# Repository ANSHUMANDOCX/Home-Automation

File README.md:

# ESP32 Home automation
## Description 
- This is a ESP32 S3 Based Home Automation devices which has 6 Relay switches that can be controlled over the web 
- It also has a BME280 Sensor for monitoring temprature,humidity and pressure in the realtime and can be monitored using a mobile app or a Webpage.
- Also had a FTDI header for easy programming
- Along with web control there is provison to add any physical switches and the case has space to add touch switches too
## Parts Used
- ESP32 S3
- BME280 Sensor
- 6 relays
- Hi-Link 20w 5v AC-DC converter
## Usage 
it is very simple to use just need to plugin the FTDI programmer and Upload the code after adding your SSID nad password so that it will work and on you browser open 192.168.1.100 ive set this as the static IP for accessing the webpage running on the ESP

## PCB Schematic and CAD 

## BUILD 

demo link https://drive.google.com/file/d/14zfI7igBqzAfgmiqQ8RciHNbKA9al0T5/view?usp=sharing

## BOM 
| Name                     | Purpose                     | Quantity | Total Cost (USD) | Link                                                                 | Distributor |
|--------------------------|----------------------------|----------|------------------|----------------------------------------------------------------------|-------------|
| Passive Components       | Ressitor and ETC           | 1        | 3.00             |                                                                      | LCSC        |
| BWGMRJWX50-10WJ          | Antenna Stem               | 1        | 0.94             |                                                                      | LCSC        |
| BWIPX1-SMA-1.13L100      | Antenna                    | 1        | 0.94             |                                                                      | LCSC        |
| MIC5219-3.3YM5-TD        | 3.3v Regulator             | 1        | 1.23             | https://www.lcsc.com/product-detail/C42422052.html                  | LCSC        |
| SMBJ5.0A                 | TVS diode                  | 1        | 0.50             | https://www.lcsc.com/product-detail/C83333.html                     | LCSC        |
| DB128V-5.0-2P-BK-S       | Terminal Block 2P          | 1        | 0.80             | https://www.lcsc.com/product-detail/C424692.html                    | LCSC        |
| 1N4007 M7                | Diode                      | 1        | 0.64             | https://www.lcsc.com/product-detail/C20754788.html                  | LCSC        |
| TS665CJ                  | Switch                     | 1        | 0.83             | https://www.lcsc.com/product-detail/C393938.html                    | LCSC        |
| DB128V-5.08-3P-GN-S      | Terminal Block 3P          | 1        | 1.45             | https://www.lcsc.com/product-detail/C2915640.html                   | LCSC        |
| MOV14D471K206RV080       | its a MOV for protection   | 1        | 0.52             | https://www.lcsc.com/product-detail/C22390366.html                  | LCSC        |
| ESP32-S3-WROOM-1-N4      | the brains                 | 1        | 4.64             | https://www.lcsc.com/product-detail/C2913197.html                   | LCSC        |
| BME280                   | Sensor                     | 1        | 7.24             | https://www.lcsc.com/product-detail/C92489.html                     | LCSC        |
| Relay 5v                 | to switch                  | 6        | 2.88             | https://www.lcsc.com/product-detail/C35449.html                     | LCSC        |
| PC817C                   | optocoupler                | 1        | 0.55             | https://www.lcsc.com/product-detail/C20612594.html                  | LCSC        |
| HLK-20M05                | onboard 5v                 | 1        | 4.58             | https://www.lcsc.com/product-detail/C465406.html                    | LCSC        |

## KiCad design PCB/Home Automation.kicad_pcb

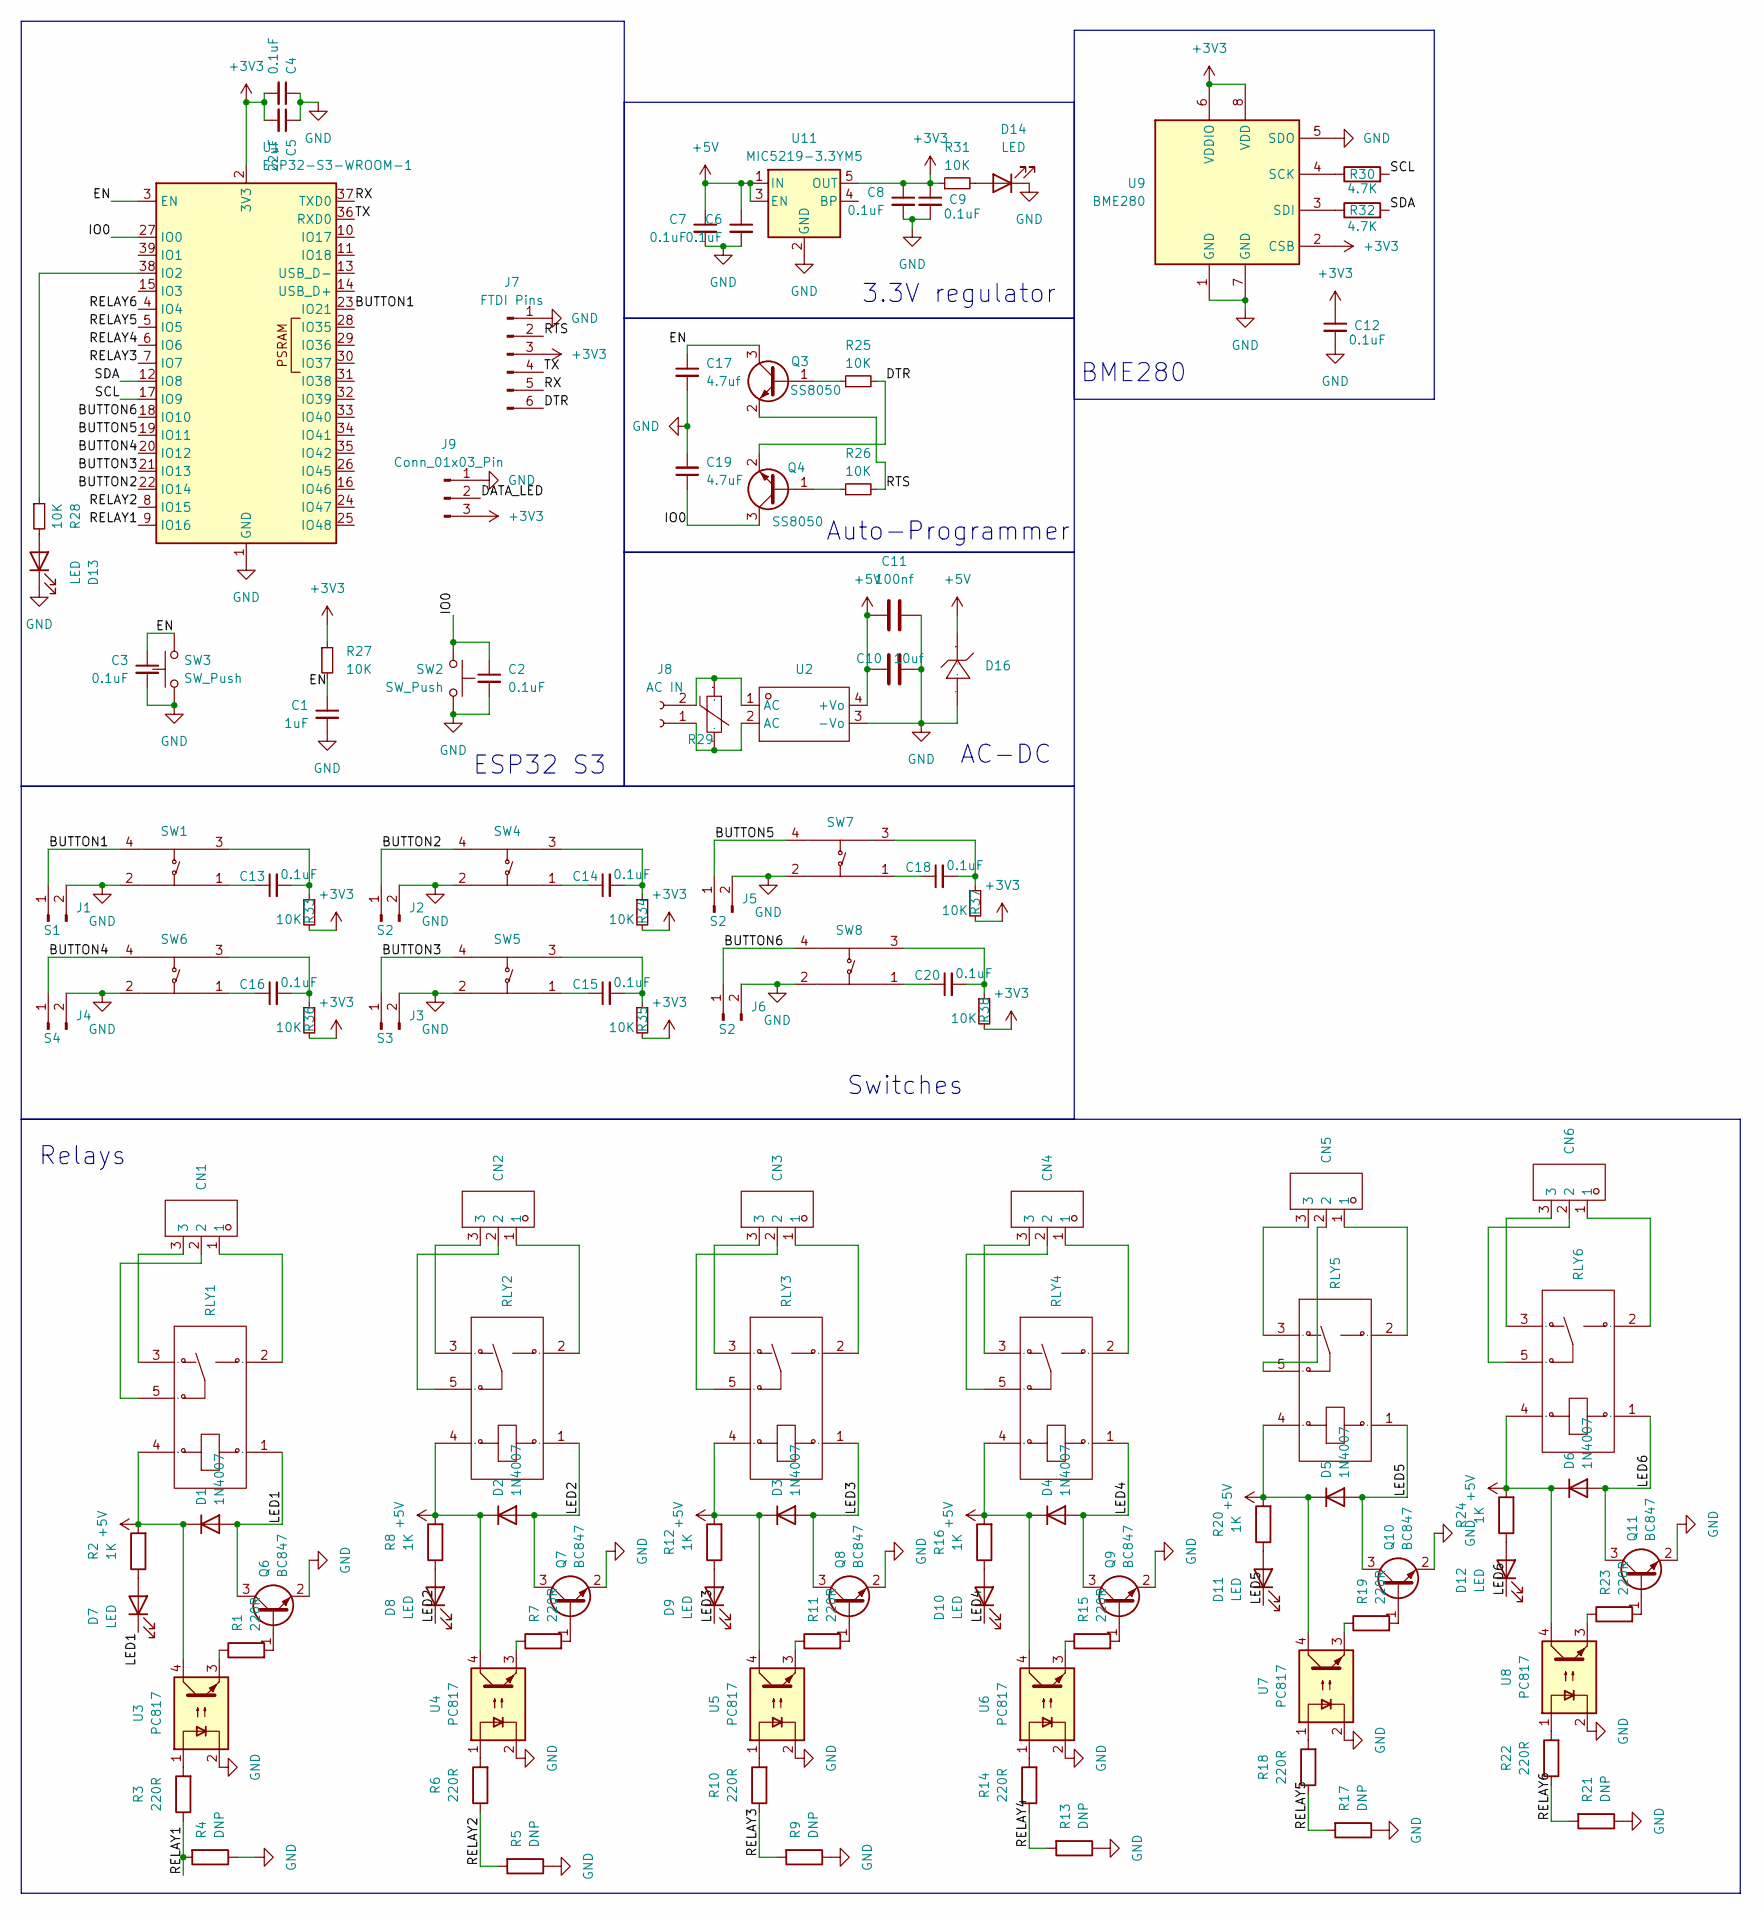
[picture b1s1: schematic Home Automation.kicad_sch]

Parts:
C1: 1uF; C_0603_1608Metric
C2, C3, C4, C6, C7, C8, C9, C12, C13, C14, C15, C16, C18, C20: 0.1uF; C_0603_1608Metric
C5: 22uF; C_0603_1608Metric
C10: 10uf; C_0603_1608Metric
C11: 100nf; C_0603_1608Metric
C17: 4.7uf; C_0603_1608Metric_Pad1.08x0.95mm_HandSolder
C19: 4.7uF; C_0603_1608Metric_Pad1.08x0.95mm_HandSolder
CN1, CN2, CN3, CN4, CN5, CN6: CONN-TH_3P-P5.08_DIBO_DB128V-5.08-3P-X; Manufacturer Part DB128V-5.08-3P-GN-S; LCSC Part Name 1x3P 5.08mm 直插 排数:1 每排P数:3
D1, D2, D3, D4, D5, D6: 1N4007; D_SMA
D7, D8, D9, D10, D11, D12, D14: LED; LED_0805_2012Metric
D13: LED; LED_0603_1608Metric_Pad1.05x0.95mm_HandSolder
D16: SMB_L4.6-W3.6-LS5.3-RD; Manufacturer Part SMBJ5.0A; LCSC Part Name SMBJ5.0A
J1: S1; PinHeader_1x02_P2.54mm_Vertical
J2, J5, J6: S2; PinHeader_1x02_P2.54mm_Vertical
J3: S3; PinHeader_1x02_P2.54mm_Vertical
J4: S4; PinHeader_1x02_P2.54mm_Vertical
J7: FTDI Pins; PinHeader_1x06_P2.54mm_Vertical
J8: AC IN; TerminalBlock_CUI_TB007-508-02_1x02_P5.08mm_Horizontal
J9: Conn_01x03_Pin; PinHeader_1x03_P2.54mm_Vertical
Q3, Q4: SS8050; SOT-23
Q6, Q7, Q8, Q9, Q10, Q11: BC847; SOT-23
R1, R3, R6, R7, R10, R11, R14, R15, R18, R19, R22, R23: 220R; R_0603_1608Metric
R2, R8, R12, R16, R20, R24: 1K; R_0603_1608Metric
R4, R5, R9, R13, R17, R21: DNP; R_0603_1608Metric
R25, R26: 10K; R_0603_1608Metric_Pad0.98x0.95mm_HandSolder
R27, R28, R31, R33, R34, R35, R36, R37, R38: 10K; R_0603_1608Metric
R29: 430pF@1kHz; RES-TH_L16.0-W5.2-P7.50-D0.8-S4.20; Manufacturer Part MOV14D471K206RV080; LCSC Part Name 14D471K
R30, R32: 4.7K; R_0603_1608Metric
RLY1, RLY2, RLY3, RLY4, RLY5, RLY6: RELAY-TH_SRD-XXVDC-XL-C; Manufacturer Part SRD-05VDC-SL-C; LCSC Part Name 蓝色 单组转换型继电器
SW1, SW4, SW5, SW6, SW7, SW8: SW-TH_4P-L6.0-W6.0-P4.50-LS6.5; Manufacturer Part TS665CJ; LCSC Part Name 6*6*5mm 直插 轻触开关
SW2, SW3: SW_Push; SW_Push_SPST_NO_Alps_SKRK
U1: ESP32-S3-WROOM-1
U2: PWRM-TH_HLK-20MXX; Manufacturer Part HLK-20M05; LCSC Part Name 20W超紧凑型电源模块系列
U3, U4, U5, U6, U7, U8: PC817; DIP-4_W7.62mm
U9: BME280; Bosch_LGA-8_2.5x2.5mm_P0.65mm_ClockwisePinNumbering
U11: MIC5219-3.3YM5; SOT-23-5

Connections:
+3V3: C4.2, C5.2, C8.1, C9.1, C12.1, J7.3, J9.3, R27.1, R31.1, R33.2, R34.2, R35.2, R36.2, R37.2, R38.2, U1.2 (3V3), U9.2 (CSB), U9.6 (VDDIO), U9.8 (VDD), U11.5 (OUT)
+5V: C6.1, C7.1, C10.1, C11.1, D1.1 (K), D2.1 (K), D3.1 (K), D4.1 (K), D5.1 (K), D6.1 (K), D16.1 (C), R2.2, R8.2, R12.2, R16.2, R20.2, R24.2, RLY1.4, RLY2.4, RLY3.4, RLY4.4, RLY5.4, RLY6.4, U2.4 (+Vo), U3.4, U4.4, U5.4, U6.4, U7.4, U8.4, U11.1 (IN), U11.3 (EN)
/BUTTON1: J1.1, SW1.4 (D), U1.23 (IO21)
/BUTTON2: J2.1, SW4.4 (D), U1.22 (IO14)
/BUTTON3: J3.1, SW5.4 (D), U1.21 (IO13)
/BUTTON4: J4.1, SW6.4 (D), U1.20 (IO12)
/BUTTON5: J5.1, SW7.4 (D), U1.19 (IO11)
/BUTTON6: J6.1, SW8.4 (D), U1.18 (IO10)
/DTR: J7.6, Q4.2 (E), R25.2
/EN: C1.1, C3.1, C17.1, Q3.3 (C), R27.2, SW3.2, U1.3 (EN)
/IO0: C2.1, C19.1, Q4.3 (C), SW2.2, U1.27 (IO0)
/LED1: D1.2 (A), D7.1 (K), Q6.3 (C), RLY1.1
/LED2: D2.2 (A), D8.1 (K), Q7.3 (C), RLY2.1
/LED3: D3.2 (A), D9.1 (K), Q8.3 (C), RLY3.1
/LED4: D4.2 (A), D10.1 (K), Q9.3 (C), RLY4.1
/LED5: D5.2 (A), D11.1 (K), Q10.3 (C), RLY5.1
/LED6: D6.2 (A), D12.1 (K), Q11.3 (C), RLY6.1
/RELAY1: R3.1, R4.2, U1.9 (IO16)
/RELAY2: R5.2, R6.1, U1.8 (IO15)
/RELAY3: R9.2, R10.1, U1.7 (IO7)
/RELAY4: R13.2, R14.1, U1.6 (IO6)
/RELAY5: R17.2, R18.1, U1.5 (IO5)
/RELAY6: R21.2, R22.1, U1.4 (IO4)
/RTS: J7.2, Q3.2 (E), R26.2
/RX: J7.5, U1.37 (TXD0)
/SCL: R30.2, U1.17 (IO9)
/SDA: R32.2, U1.12 (IO8)
/TX: J7.4, U1.36 (RXD0)
GND: C1.2, C2.2, C3.2, C4.1, C5.1, C6.2, C7.2, C8.2, C9.2, C10.2, C11.2, C12.2, C17.2, C19.2, D13.1 (K), D14.1 (K), D16.2 (A), J1.2, J2.2, J3.2, J4.2, J5.2, J6.2, J7.1, J9.1, Q6.2 (E), Q7.2 (E), Q8.2 (E), Q9.2 (E), Q10.2 (E), Q11.2 (E), R4.1, R5.1, R9.1, R13.1, R17.1, R21.1, SW1.2 (B), SW2.1, SW3.1, SW4.2 (B), SW5.2 (B), SW6.2 (B), SW7.2 (B), SW8.2 (B), U1.1 (GND), U1.40 (GND), U1.41 (GND), U2.3 (-Vo), U3.2, U4.2, U5.2, U6.2, U7.2, U8.2, U9.1 (GND), U9.5 (SDO), U9.7 (GND), U11.2 (GND)
unnamed: CN1.1, RLY1.2
unnamed: CN1.2, RLY1.5
unnamed: CN1.3, RLY1.3
unnamed: CN2.1, RLY2.2
unnamed: CN2.2, RLY2.5
unnamed: CN2.3, RLY2.3
unnamed: CN3.1, RLY3.2
unnamed: CN3.2, RLY3.5
unnamed: CN3.3, RLY3.3
unnamed: CN4.1, RLY4.2
unnamed: CN4.2, RLY4.5
unnamed: CN4.3, RLY4.3
unnamed: CN5.1, RLY5.2
unnamed: CN5.2, RLY5.5
unnamed: CN5.3, RLY5.3
unnamed: CN6.1, RLY6.2
unnamed: CN6.2, RLY6.5
unnamed: CN6.3, RLY6.3
unnamed: D7.2 (A), R2.1
unnamed: D8.2 (A), R8.1
unnamed: D9.2 (A), R12.1
unnamed: D10.2 (A), R16.1
unnamed: D11.2 (A), R20.1
unnamed: D12.2 (A), R24.1
unnamed: D13.2 (A), R28.2
unnamed: D14.2 (A), R31.2
unnamed: Q3.1 (B), R25.1
unnamed: Q4.1 (B), R26.1
unnamed: Q6.1 (B), R1.2
unnamed: Q7.1 (B), R7.2
unnamed: Q8.1 (B), R11.2
unnamed: Q9.1 (B), R15.2
unnamed: Q10.1 (B), R19.2
unnamed: Q11.1 (B), R23.2
unnamed: R1.1, U3.3
unnamed: R3.2, U3.1
unnamed: R6.2, U4.1
unnamed: R7.1, U4.3
unnamed: R10.2, U5.1
unnamed: R11.1, U5.3
unnamed: R14.2, U6.1
unnamed: R15.1, U6.3
unnamed: R18.2, U7.1
unnamed: R19.1, U7.3
unnamed: R22.2, U8.1
unnamed: R23.1, U8.3
unnamed: C13.1, SW1.1 (A)
unnamed: C13.2, R33.1, SW1.3 (C)
unnamed: C14.1, SW4.1 (A)
unnamed: C14.2, R34.1, SW4.3 (C)
unnamed: C15.1, SW5.1 (A)
unnamed: C15.2, R35.1, SW5.3 (C)
unnamed: C16.1, SW6.1 (A)
unnamed: C16.2, R36.1, SW6.3 (C)
unnamed: C18.1, SW7.1 (A)
unnamed: C18.2, R37.1, SW7.3 (C)
unnamed: C20.1, SW8.1 (A)
unnamed: C20.2, R38.1, SW8.3 (C)
unnamed: R28.1, U1.38 (IO2)
unnamed: R30.1, U9.4 (SCK)
unnamed: R32.1, U9.3 (SDI)

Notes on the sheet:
AC-DC
Relays
BME280
Switches
ESP32 S3
Auto-Programmer
3.3V regulator

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
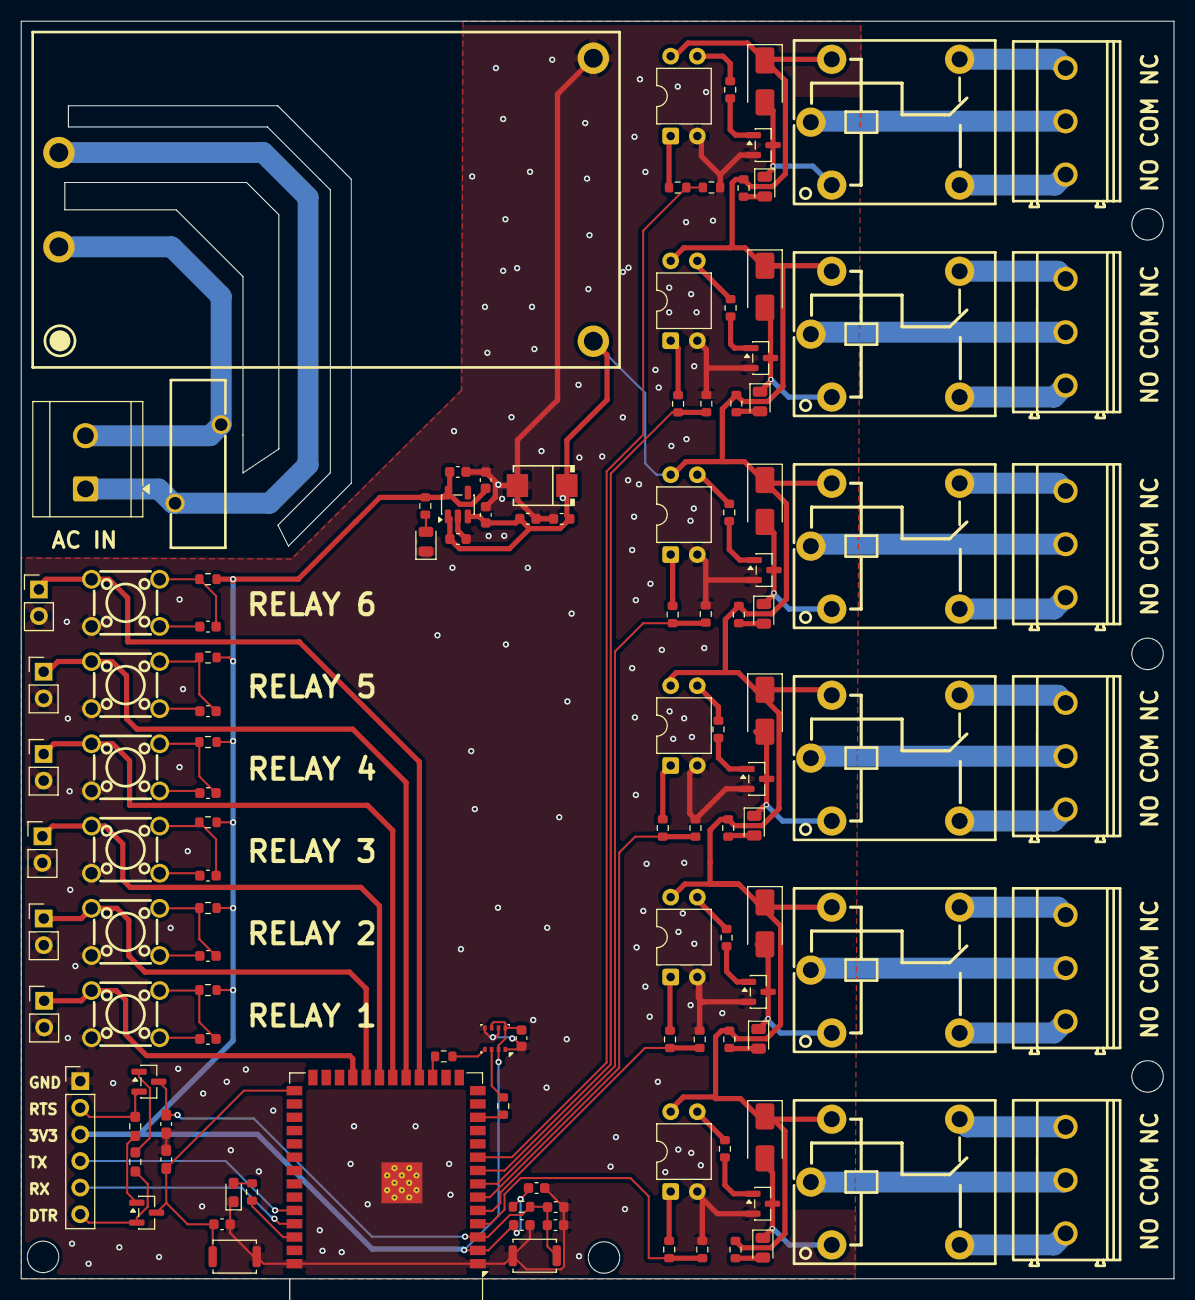
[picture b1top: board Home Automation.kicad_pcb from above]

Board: 2 copper layers, 110.0 x 120.0 mm, 119 parts (0 on the bottom side), 92 nets.

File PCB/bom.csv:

Designator,Footprint,Quantity,Value,LCSC Part #
C1,0603,1,1uF,
C10,0603,1,10uf,
C11,0603,1,100nf,
"C12, C13, C14, C15, C16, C18, C2, C20, C3, C4, C6, C7, C8, C9",0603,14,0.1uF,
"C17, C19",0603,2,4.7uf,
C5,0603,1,22uF,
"CN1, CN2, CN3, CN4, CN5, CN6",CONN-TH_3P-P5.08_DIBO_DB128V-5.08-3P-X,6,~,
"D1, D2, D3, D4, D5, D6",D_SMA,6,1N4007,
"D10, D11, D12, D14, D7, D8, D9",0805,7,LED,
D13,0603,1,LED,
D16,SMB_L4.6-W3.6-LS5.3-RD,1,~,
J1,PinHeader_1x02_P2.54mm_Vertical,1,S1,
"J2, J5, J6",PinHeader_1x02_P2.54mm_Vertical,3,S2,
J3,PinHeader_1x02_P2.54mm_Vertical,1,S3,
J4,PinHeader_1x02_P2.54mm_Vertical,1,S4,
J7,PinHeader_1x06_P2.54mm_Vertical,1,FTDI Pins,
J8,TerminalBlock_CUI_TB007-508-02_1x02_P5.08mm_Horizontal,1,AC IN,
"Q10, Q11, Q6, Q7, Q8, Q9",SOT-23,6,BC847,
"Q3, Q4",SOT-23,2,SS8050,
"R1, R10, R11, R14, R15, R18, R19, R22, R23, R3, R6, R7",0603,12,220R,
"R12, R16, R2, R20, R24, R8",0603,6,1K,
"R13, R17, R21, R4, R5, R9",0603,6,DNP,
"R25, R26, R27, R28, R31, R33, R34, R35, R36, R37, R38",0603,11,10K,
R29,RES-TH_L16.0-W5.2-P7.50-D0.8-S4.20,1,430pF@1kHz,
"R30, R32",0603,2,4.7K,
"RLY1, RLY2, RLY3, RLY4, RLY5, RLY6",RELAY-TH_SRD-XXVDC-XL-C,6,~,
"SW1, SW4, SW5, SW6, SW7, SW8",SW-TH_4P-L6.0-W6.0-P4.50-LS6.5,6,~,
"SW2, SW3",SW_Push_SPST_NO_Alps_SKRK,2,SW_Push,
U1,ESP32-S3-WROOM-1,1,ESP32-S3-WROOM-1,
U11,SOT-23-5,1,MIC5219-3.3YM5,
U2,PWRM-TH_HLK-20MXX,1,~,
"U3, U4, U5, U6, U7, U8",DIP-4_W7.62mm,6,PC817,
U9,Bosch_LGA-8_2.5x2.5mm_P0.65mm_ClockwisePinNumbering,1,BME280,

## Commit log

2026-06-15 Enhance README with usage, build images, and demo link
    Updated usage instructions and added build images and demo link.
